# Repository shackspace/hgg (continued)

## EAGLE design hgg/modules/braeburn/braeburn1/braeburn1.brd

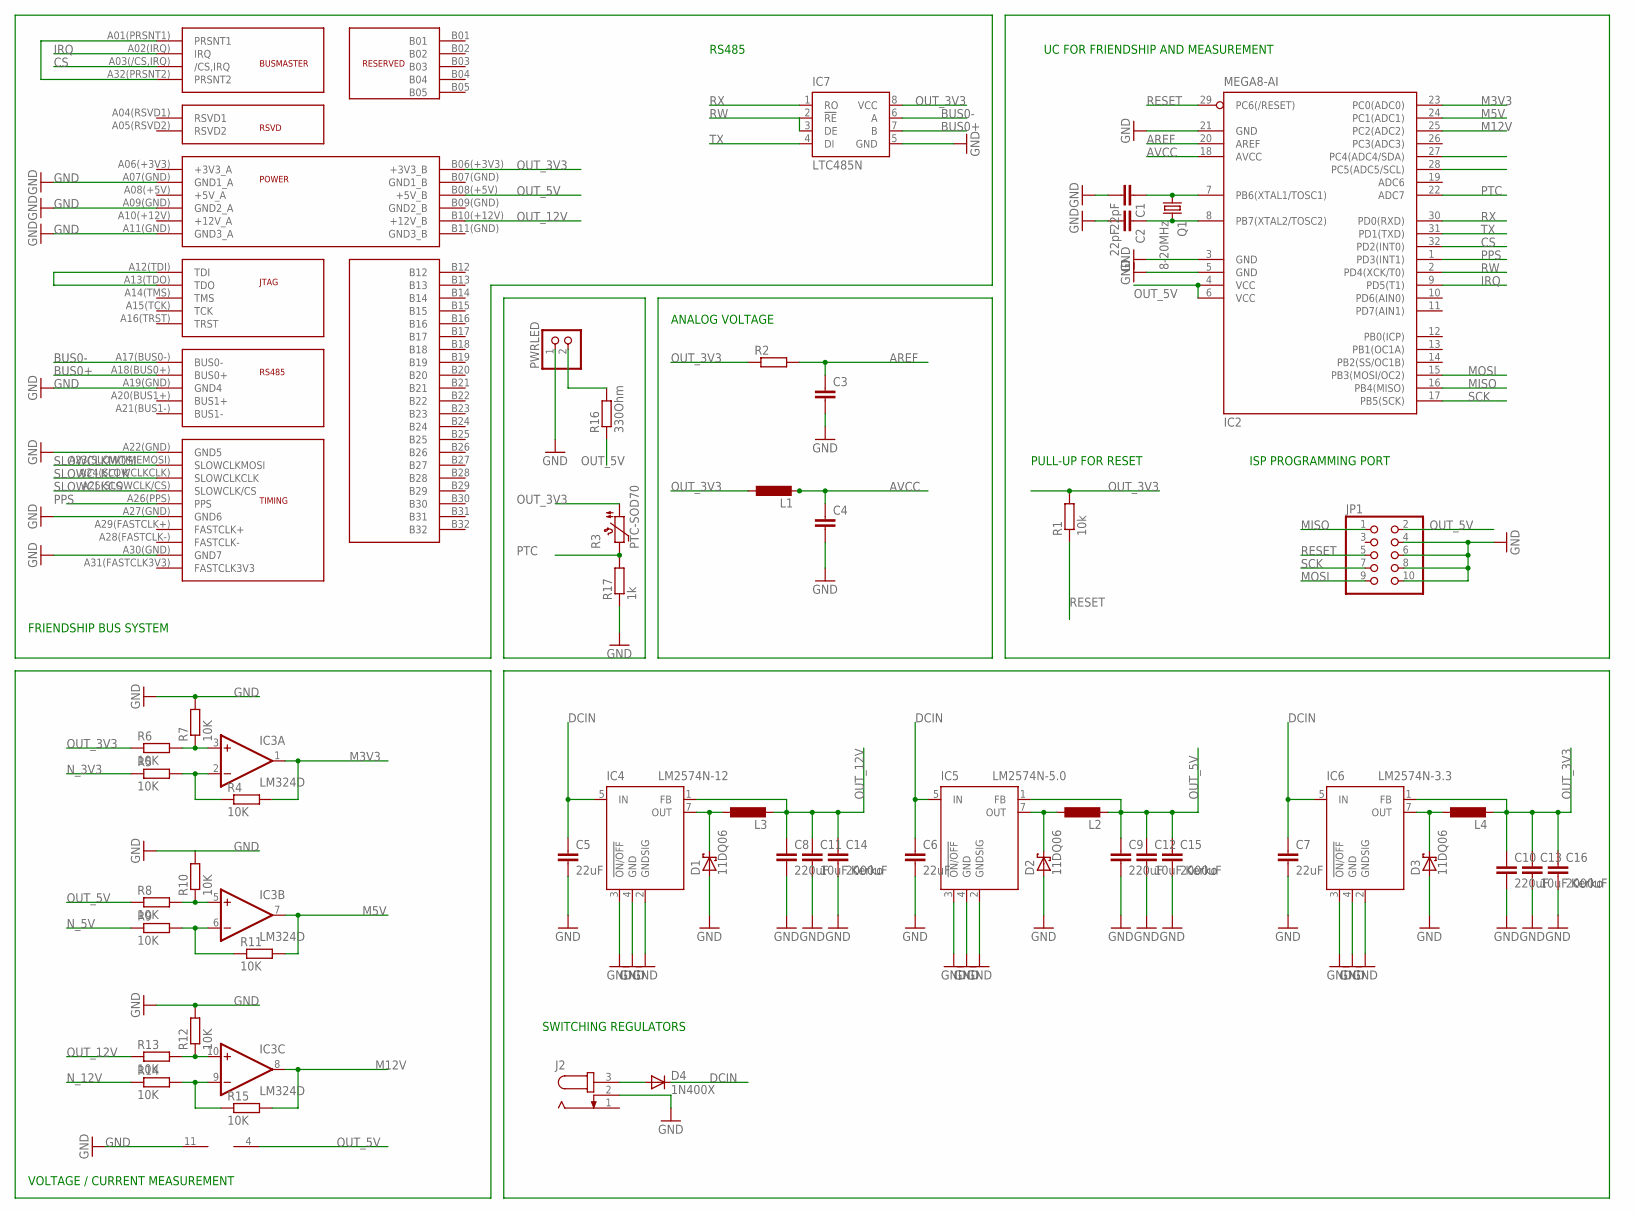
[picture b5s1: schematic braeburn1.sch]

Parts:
C1, C2: 22pF; C0603
C3, C4: C-EUC0603; C0603
C5, C6, C7: 22uF; C025-050X050
C8, C9, C10: 220uF; C025-050X050
C11, C12, C13: 10uF Kerko; C0603
C14, C15, C16: 2000uF; C050-075X075
D1, D2, D3: 11DQ06; DO41-7.6
D4: 1N400X; DO41-10
IC2: MEGA8-AI; TQFP32-08
IC3: LM324D; SO14
IC4: LM2574N-12; DIL08
IC5: LM2574N-5.0; DIL08
IC6: LM2574N-3.3; DIL08
IC7: LTC485N; DIL08
J2: JACK-PLUG0; SPC4077
JP1: PINHD-2X5; 2X05
L1: L-EU0207/5V; 0207/5V
L2, L3, L4: L-EUPIS2816; PIS2816
PWRLED: PINHD-1X2; 1X02
Q1: 8-20MHz; HC49/S
R1: 10k; R0603
R2: R-EU_R0603; R0603
R3: PTC-SOD70; SOD70
R4, R5, R6, R7, R8, R9, R10, R11, R12, R13, R14, R15: 10K; R0603
R16: 330Ohm; R0603
R17: 1k; 0207/12
U$1: FRIENDSHIPCONNECTOR; FRIENDSHIP_EDGE_CONNECTOR

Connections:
AREF: C3.1, IC2.20 (AREF), R2.2
AVCC: C4.1, IC2.18 (AVCC), L1.2
BUS0+: IC7.7 (B), U$1.A18(BUS0+) (BUS0+)
BUS0-: IC7.6 (A), U$1.A17(BUS0-) (BUS0-)
CS: IC2.32 (PD2(INT0)), U$1.A03(/CS,IRQ) (/CS,IRQ)
DCIN: C5.1, C6.1, C7.1, D4.C, IC4.5 (IN), IC5.5 (IN), IC6.5 (IN)
GND: C1.2, C2.2, C3.2, C4.2, C5.2, C6.2, C7.2, C8.2, C9.2, C10.2, C11.2, C12.2, C13.2, C14.2, C15.2, C16.2, D1.A, D2.A, D3.A, IC2.3 (GND), IC2.5 (GND), IC2.21 (GND), IC3.11 (V-), IC4.2 (GNDSIG), IC4.3 (!ON/OFF), IC4.4 (GND), IC5.2 (GNDSIG), IC5.3 (!ON/OFF), IC5.4 (GND), IC6.2 (GNDSIG), IC6.3 (!ON/OFF), IC6.4 (GND), IC7.5 (GND), J2.2, JP1.4, JP1.6, JP1.8, JP1.10, PWRLED.1, R7.2, R10.2, R12.2, R17.1, U$1.A07(GND) (GND1_A), U$1.A09(GND) (GND2_A), U$1.A11(GND) (GND3_A), U$1.A19(GND) (GND4), U$1.A22(GND) (GND5), U$1.A30(GND) (GND7)
IRQ: IC2.9 (PD5(T1)), U$1.A02(IRQ) (IRQ)
M3V3: IC2.23 (PC0(ADC0)), IC3.1 (OUT), R4.2
M5V: IC2.24 (PC1(ADC1)), IC3.7 (OUT), R11.2
M12V: IC2.25 (PC2(ADC2)), IC3.8 (OUT), R15.2
MISO: IC2.16 (PB4(MISO)), JP1.1
MOSI: IC2.15 (PB3(MOSI/OC2)), JP1.9
unnamed: U$1.A01(PRSNT1) (PRSNT1), U$1.A32(PRSNT2) (PRSNT2)
unnamed: U$1.A12(TDI) (TDI), U$1.A13(TDO) (TDO)
unnamed: C1.1, IC2.7 (PB6(XTAL1/TOSC1)), Q1.1
unnamed: C2.1, IC2.8 (PB7(XTAL2/TOSC2)), Q1.2
unnamed: IC3.2 (-IN), R4.1, R5.2
unnamed: IC3.3 (+IN), R6.2, R7.1
unnamed: IC3.6 (-IN), R9.2, R11.1
unnamed: D4.A, J2.3
unnamed: IC3.5 (+IN), R8.2, R10.1
unnamed: PWRLED.2, R16.2
unnamed: IC3.10 (+IN), R12.1, R13.2
unnamed: IC3.9 (-IN), R14.2, R15.1
N_3V3: D3.C, IC6.7 (OUT), L4.1, R5.1
N_5V: D2.C, IC5.7 (OUT), L2.1, R9.1
N_12V: D1.C, IC4.7 (OUT), L3.1, R14.1
OUT_3V3: C10.1, C13.1, C16.1, IC6.1 (FB), IC7.8 (VCC), L1.1, L4.2, R1.2, R2.1, R3.1, R6.1, U$1.B06(+3V3) (+3V3_B)
OUT_5V: C9.1, C12.1, C15.1, IC2.4 (VCC), IC2.6 (VCC), IC3.4 (V+), IC5.1 (FB), JP1.2, L2.2, R8.1, R16.1, U$1.B08(+5V) (+5V_B)
OUT_12V: C8.1, C11.1, C14.1, IC4.1 (FB), L3.2, R13.1, U$1.B10(+12V) (+12V_B)
PPS: IC2.1 (PD3(INT1)), U$1.A26(PPS) (PPS)
PTC: IC2.22 (ADC7), R3.2, R17.2
RESET: IC2.29 (PC6(/RESET)), JP1.5, R1.1
RW: IC2.2 (PD4(XCK/T0)), IC7.2 (!RE), IC7.3 (DE)
RX: IC2.30 (PD0(RXD)), IC7.1 (RO)
SCK: IC2.17 (PB5(SCK)), JP1.7
SLOWCLKCLK: U$1.A24(SLOWCLKCLK) (SLOWCLKCLK)
SLOWCLKCS: U$1.A25(SLOWCLK/CS) (SLOWCLK/CS)
SLOWCLKMOSI: U$1.A23(SLOWTIMEMOSI) (SLOWCLKMOSI)
TX: IC2.31 (PD1(TXD)), IC7.4 (DI)

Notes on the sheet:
FRIENDSHIP BUS SYSTEM
RS485
PULL-UP FOR RESET
ISP PROGRAMMING PORT
UC FOR FRIENDSHIP AND MEASUREMENT
ANALOG VOLTAGE
VOLTAGE / CURRENT MEASUREMENT
SWITCHING REGULATORS

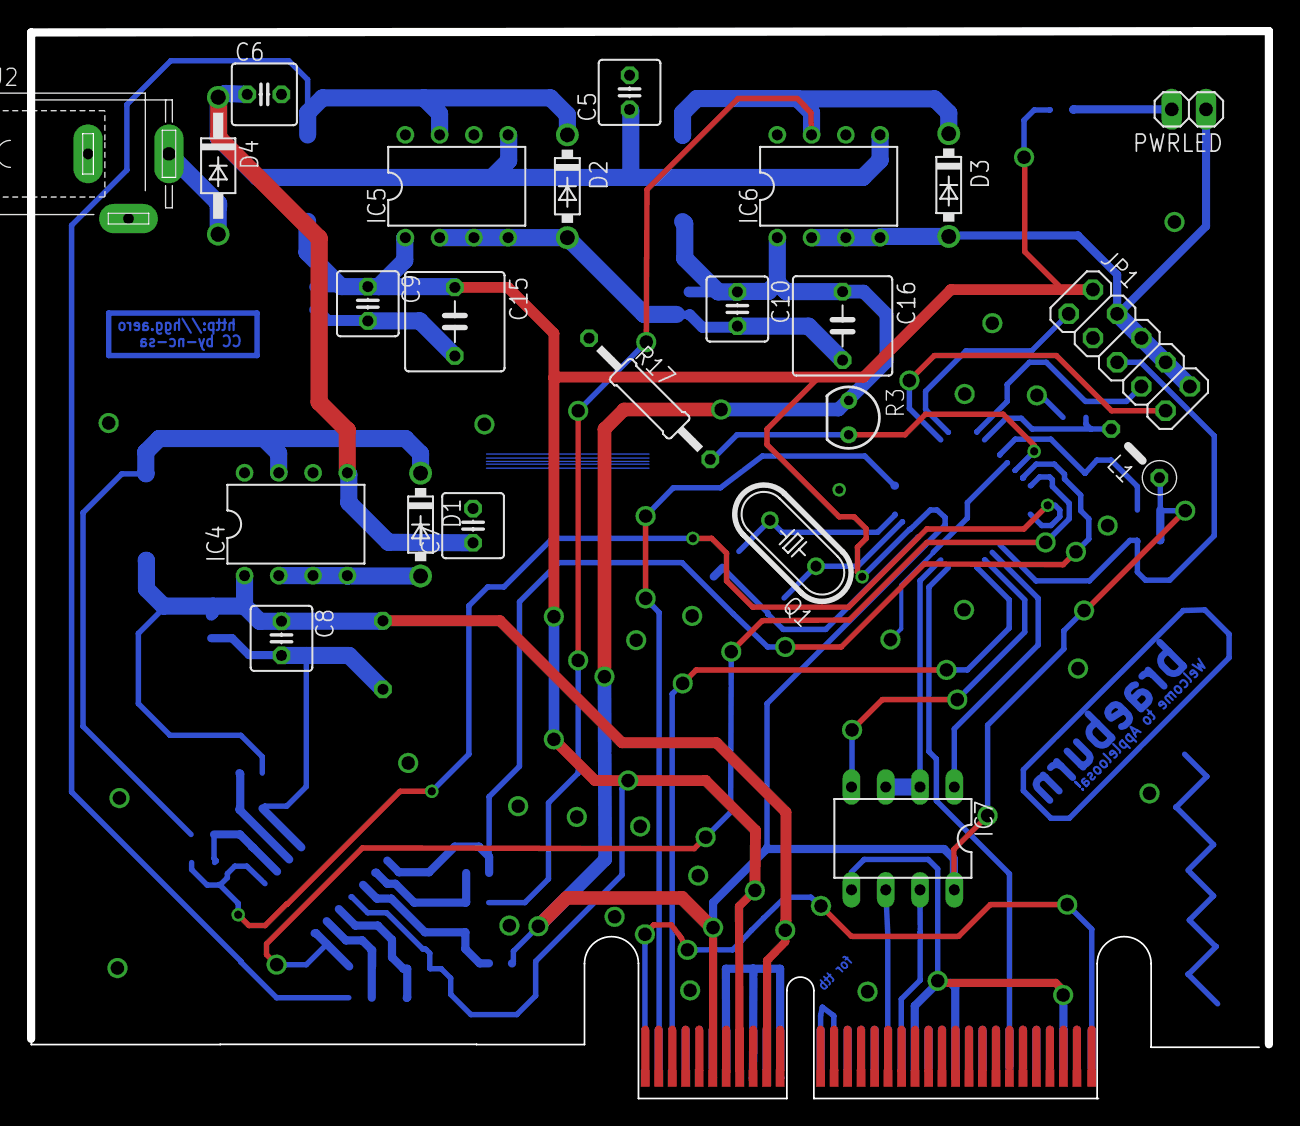
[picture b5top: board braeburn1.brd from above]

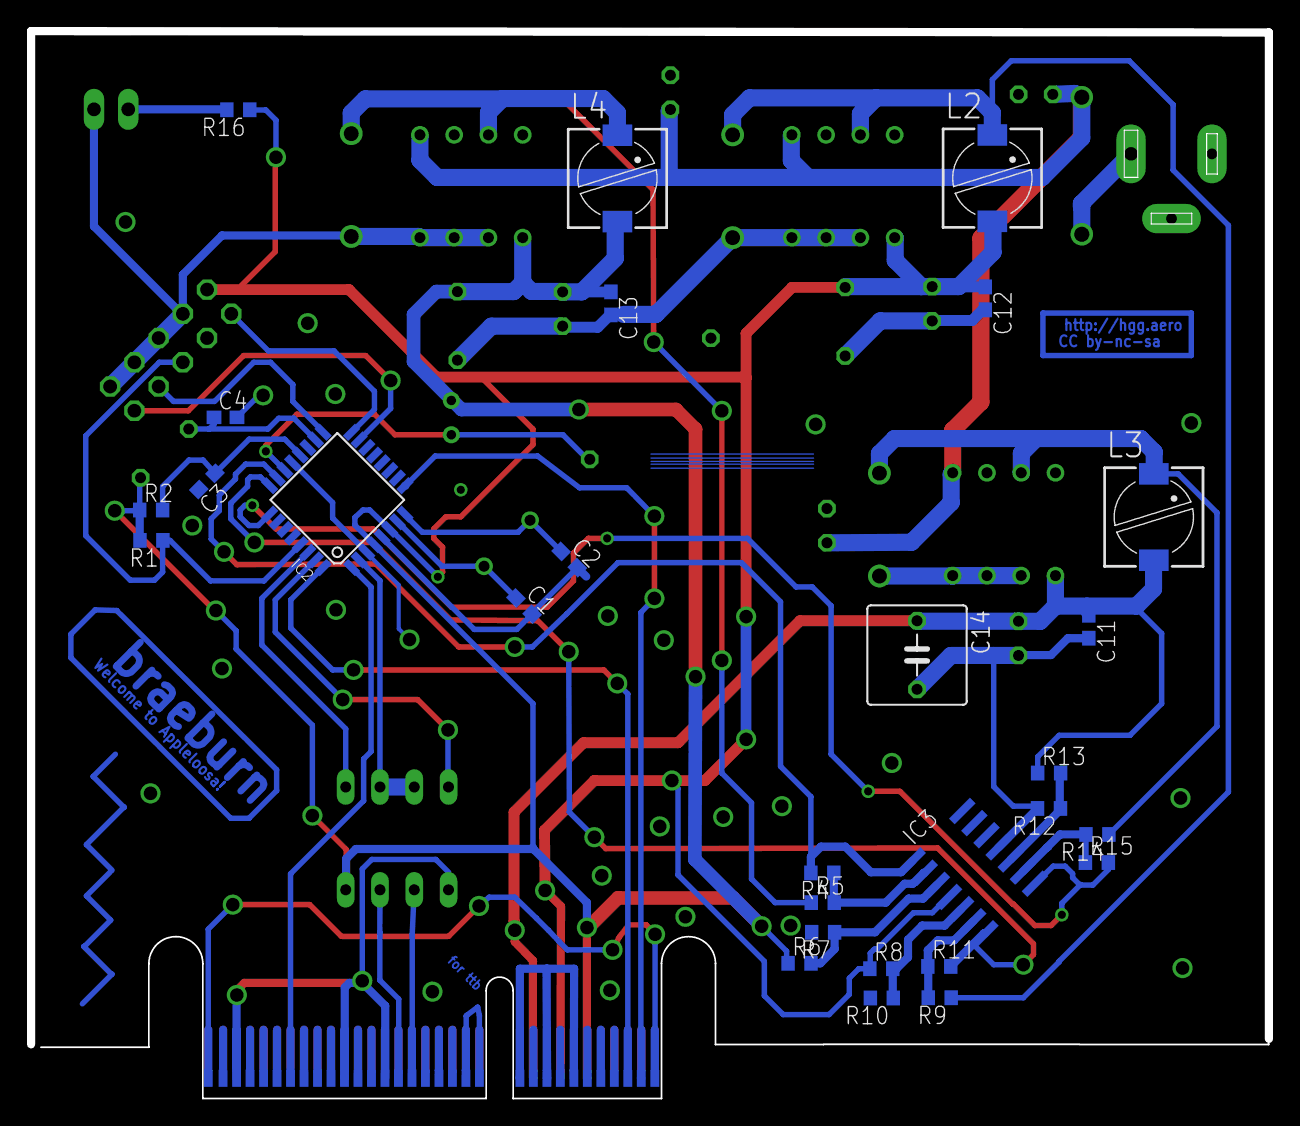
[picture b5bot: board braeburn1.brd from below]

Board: 2 copper layers, 91.8 x 79.1 mm, 52 parts (28 on the bottom side), 38 nets.

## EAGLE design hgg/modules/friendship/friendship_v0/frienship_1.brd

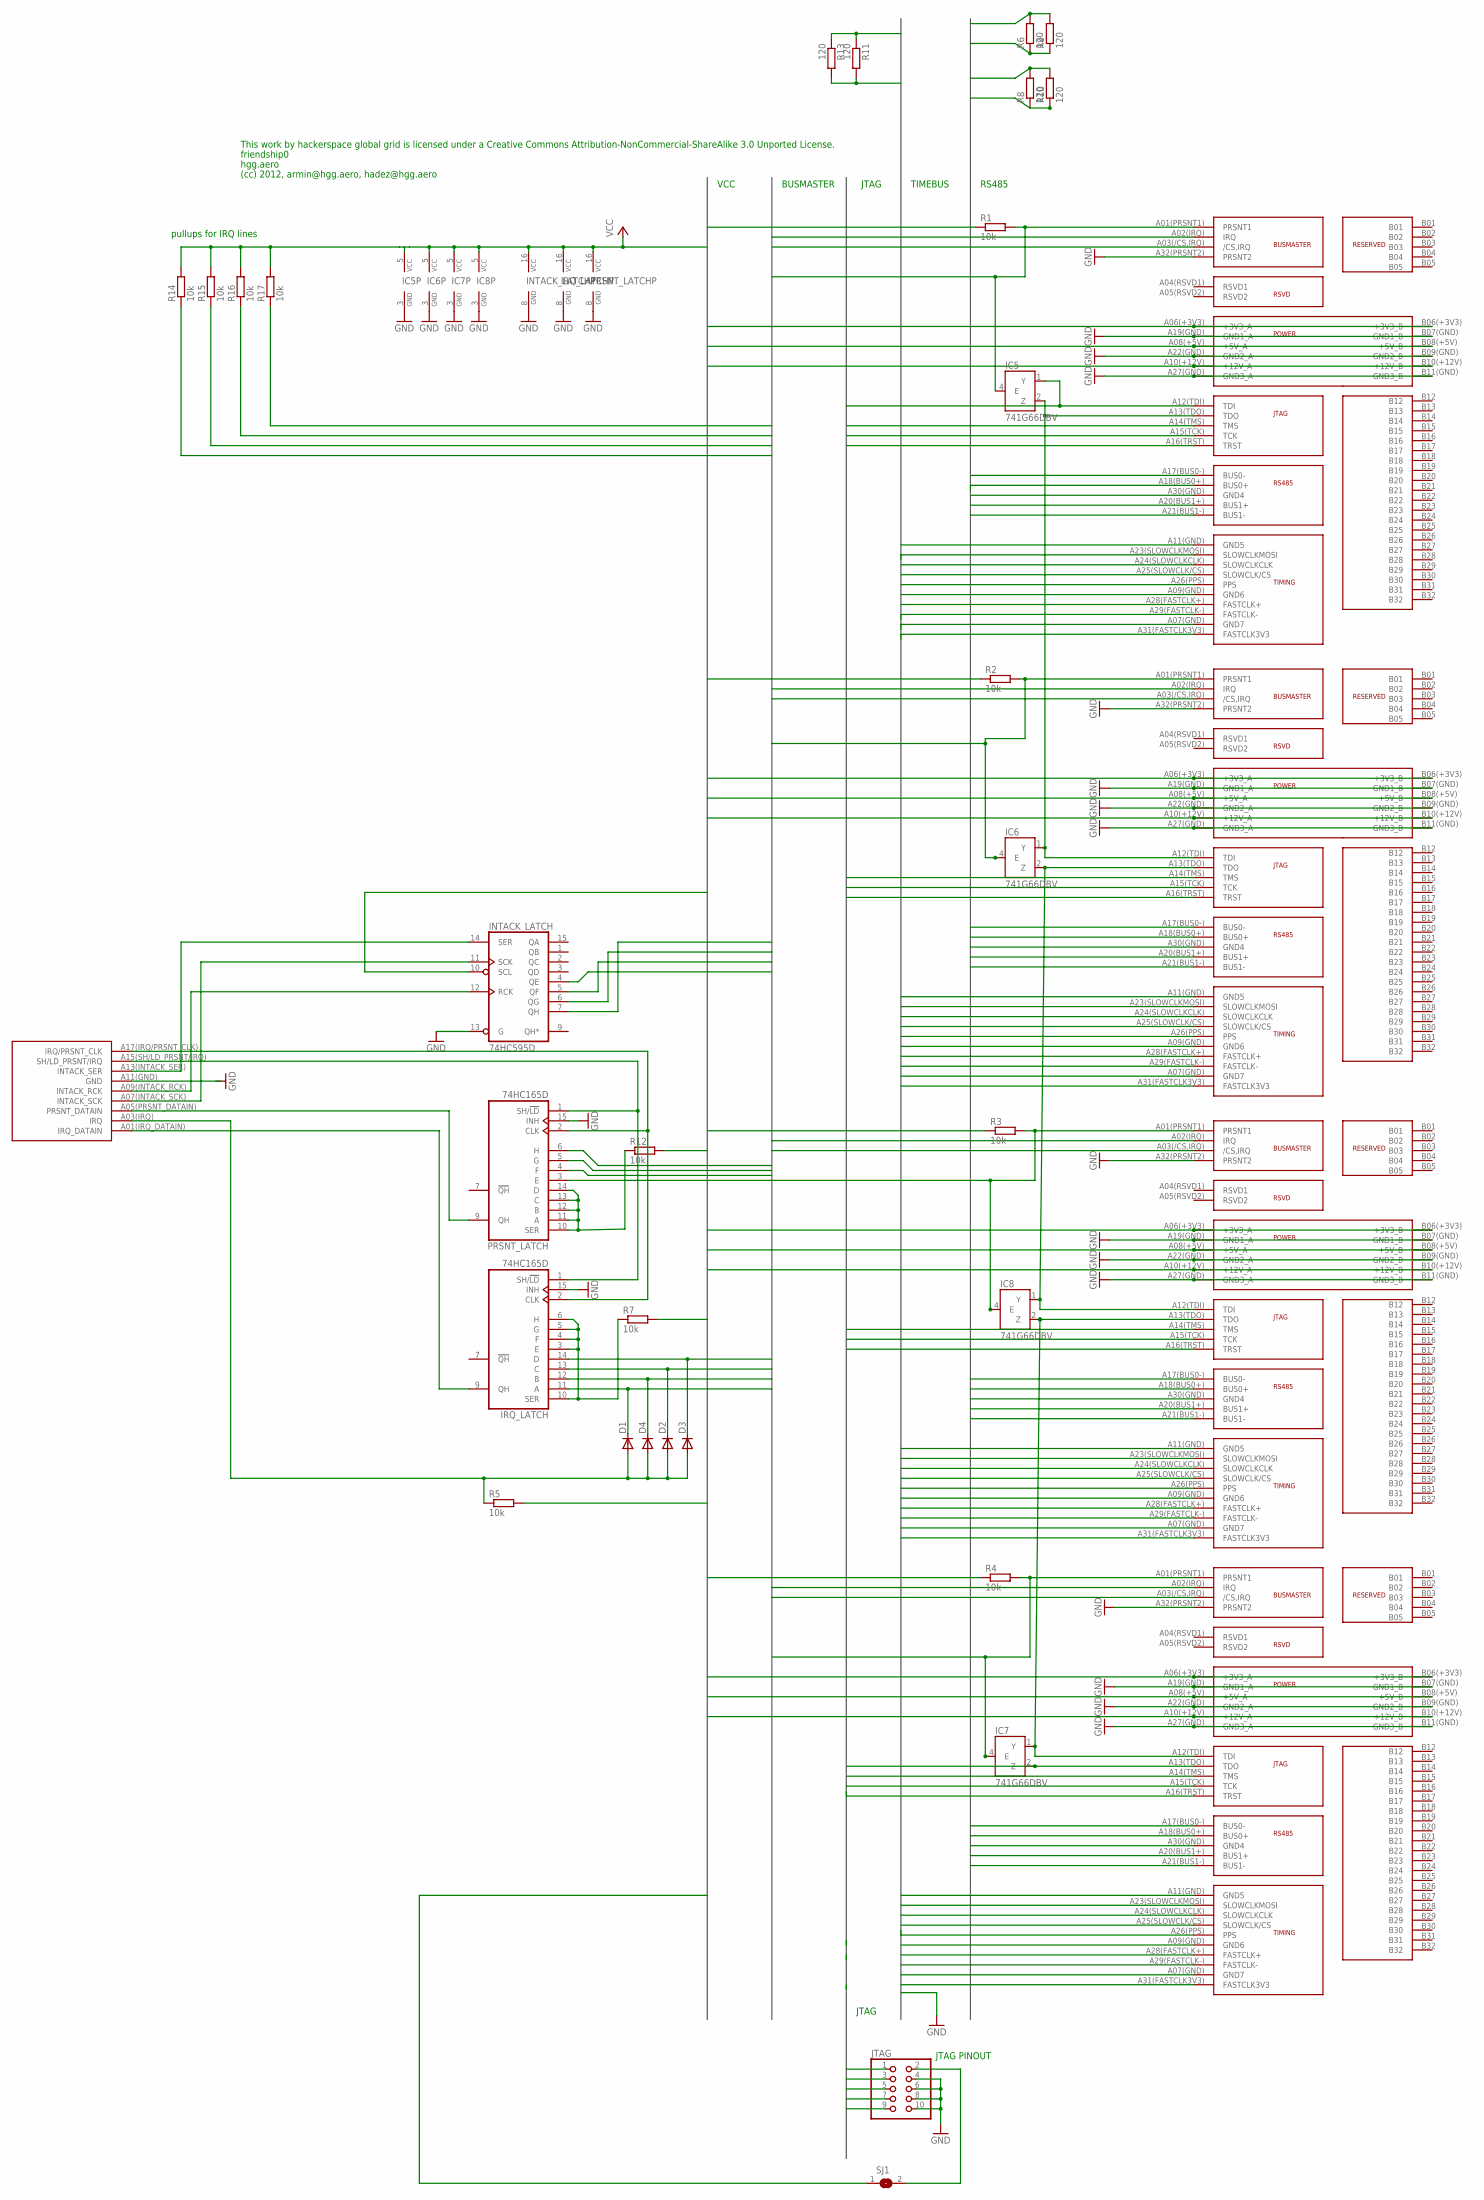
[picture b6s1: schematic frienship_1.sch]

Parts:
D1, D2, D3, D4: DIODE-SOD80C; SOD80C
IC5, IC6, IC7, IC8: 741G66DBV; SOT23-5
INTACK_LATCH: 74HC595D; SO16
IRQ_LATCH: 74HC165D; SO16
JTAG: PINHD-2X5; 2X05
PORT0, PORT1, PORT2, PORT3: FRIENDSHIPSLOT; FRIENDSHIP_SLOT
PRSNT_LATCH: 74HC165D; SO16
R1, R2, R3, R4, R5, R7, R12, R14, R15, R16, R17: 10k; R0603
R6, R8, R9, R10, R11, R13: 120; R0603
SJ1: SJ
U$1: BUSMASTER_PLUG; BUSMASTER_SLOT

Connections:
3V3: IC5.5 (VCC), IC6.5 (VCC), IC7.5 (VCC), IC8.5 (VCC), INTACK_LATCH.10 (SCL), INTACK_LATCH.16 (VCC), IRQ_LATCH.16 (VCC), PORT0.A06(+3V3) (+3V3_A), PORT0.B06(+3V3) (+3V3_B), PORT1.A06(+3V3) (+3V3_A), PORT1.B06(+3V3) (+3V3_B), PORT2.A06(+3V3) (+3V3_A), PORT2.B06(+3V3) (+3V3_B), PORT3.A06(+3V3) (+3V3_A), PORT3.B06(+3V3) (+3V3_B), PRSNT_LATCH.16 (VCC), R1.1, R2.1, R3.1, R4.1, R5.2, R7.2, R12.2, R14.2, R15.2, R16.2, R17.2, SJ1.1
5V: PORT0.A08(+5V) (+5V_A), PORT0.B08(+5V) (+5V_B), PORT1.A08(+5V) (+5V_A), PORT1.B08(+5V) (+5V_B), PORT2.A08(+5V) (+5V_A), PORT2.B08(+5V) (+5V_B), PORT3.A08(+5V) (+5V_A), PORT3.B08(+5V) (+5V_B)
12V: PORT0.A10(+12V) (+12V_A), PORT0.B10(+12V) (+12V_B), PORT1.A10(+12V) (+12V_A), PORT1.B10(+12V) (+12V_B), PORT2.A10(+12V) (+12V_A), PORT2.B10(+12V) (+12V_B), PORT3.A10(+12V) (+12V_A), PORT3.B10(+12V) (+12V_B)
/CS: PORT0.A25(SLOWCLK/CS) (SLOWCLK/CS), PORT1.A25(SLOWCLK/CS) (SLOWCLK/CS), PORT2.A25(SLOWCLK/CS) (SLOWCLK/CS), PORT3.A25(SLOWCLK/CS) (SLOWCLK/CS)
/CS0: INTACK_LATCH.7 (QH), PORT0.A03(/CS,IRQ) (/CS,IRQ)
/CS1: INTACK_LATCH.6 (QG), PORT1.A03(/CS,IRQ) (/CS,IRQ)
/CS2: INTACK_LATCH.5 (QF), PORT2.A03(/CS,IRQ) (/CS,IRQ)
/CS3: INTACK_LATCH.4 (QE), PORT3.A03(/CS,IRQ) (/CS,IRQ)
CLK: PORT0.A24(SLOWCLKCLK) (SLOWCLKCLK), PORT1.A24(SLOWCLKCLK) (SLOWCLKCLK), PORT2.A24(SLOWCLKCLK) (SLOWCLKCLK), PORT3.A24(SLOWCLKCLK) (SLOWCLKCLK)
FASTCLK3V3: PORT0.A31(FASTCLK3V3) (FASTCLK3V3), PORT1.A31(FASTCLK3V3) (FASTCLK3V3), PORT2.A31(FASTCLK3V3) (FASTCLK3V3), PORT3.A31(FASTCLK3V3) (FASTCLK3V3)
FASTCLK+: PORT0.A28(FASTCLK+) (FASTCLK+), PORT1.A28(FASTCLK+) (FASTCLK+), PORT2.A28(FASTCLK+) (FASTCLK+), PORT3.A28(FASTCLK+) (FASTCLK+), R11.1, R13.1
FASTCLK-: PORT0.A29(FASTCLK-) (FASTCLK-), PORT1.A29(FASTCLK-) (FASTCLK-), PORT2.A29(FASTCLK-) (FASTCLK-), PORT3.A29(FASTCLK-) (FASTCLK-), R11.2, R13.2
GND: IC5.3 (GND), IC6.3 (GND), IC7.3 (GND), IC8.3 (GND), INTACK_LATCH.8 (GND), INTACK_LATCH.13 (G), IRQ_LATCH.8 (GND), IRQ_LATCH.15 (INH), JTAG.4, JTAG.6, JTAG.8, JTAG.10, PORT0.A07(GND) (GND7), PORT0.A09(GND) (GND6), PORT0.A11(GND) (GND5), PORT0.A19(GND) (GND1_A), PORT0.A22(GND) (GND2_A), PORT0.A27(GND) (GND3_A), PORT0.A30(GND) (GND4), PORT0.A32(PRSNT2) (PRSNT2), PORT0.B07(GND) (GND1_B), PORT0.B09(GND) (GND2_B), PORT0.B11(GND) (GND3_B), PORT1.A07(GND) (GND7), PORT1.A09(GND) (GND6), PORT1.A11(GND) (GND5), PORT1.A19(GND) (GND1_A), PORT1.A22(GND) (GND2_A), PORT1.A27(GND) (GND3_A), PORT1.A30(GND) (GND4), PORT1.A32(PRSNT2) (PRSNT2), PORT1.B07(GND) (GND1_B), PORT1.B09(GND) (GND2_B), PORT1.B11(GND) (GND3_B), PORT2.A07(GND) (GND7), PORT2.A09(GND) (GND6), PORT2.A11(GND) (GND5), PORT2.A19(GND) (GND1_A), PORT2.A22(GND) (GND2_A), PORT2.A27(GND) (GND3_A), PORT2.A30(GND) (GND4), PORT2.A32(PRSNT2) (PRSNT2), PORT2.B07(GND) (GND1_B), PORT2.B09(GND) (GND2_B), PORT2.B11(GND) (GND3_B), PORT3.A07(GND) (GND7), PORT3.A09(GND) (GND6), PORT3.A11(GND) (GND5), PORT3.A19(GND) (GND1_A), PORT3.A22(GND) (GND2_A), PORT3.A27(GND) (GND3_A), PORT3.A30(GND) (GND4), PORT3.A32(PRSNT2) (PRSNT2), PORT3.B07(GND) (GND1_B), PORT3.B09(GND) (GND2_B), PORT3.B11(GND) (GND3_B), PRSNT_LATCH.8 (GND), PRSNT_LATCH.15 (INH)
IRQ0: D3.C, IRQ_LATCH.14 (D), PORT0.A02(IRQ) (IRQ), R17.1
IRQ1: D2.C, IRQ_LATCH.13 (C), PORT1.A02(IRQ) (IRQ), R16.1
IRQ2: D4.C, IRQ_LATCH.12 (B), PORT2.A02(IRQ) (IRQ), R15.1
IRQ3: D1.C, IRQ_LATCH.11 (A), PORT3.A02(IRQ) (IRQ), R14.1
MOSI: PORT0.A23(SLOWCLKMOSI) (SLOWCLKMOSI), PORT1.A23(SLOWCLKMOSI) (SLOWCLKMOSI), PORT2.A23(SLOWCLKMOSI) (SLOWCLKMOSI), PORT3.A23(SLOWCLKMOSI) (SLOWCLKMOSI)
unnamed: INTACK_LATCH.14 (SER), U$1.A13(INTACK_SER) (INTACK_SER)
unnamed: IC5.2 (Z), IC6.1 (Y), PORT0.A13(TDO) (TDO), PORT1.A12(TDI) (TDI)
unnamed: IRQ_LATCH.1 (SH/!LD), PRSNT_LATCH.1 (SH/!LD), U$1.A15(SH/LD_PRSNT/IRQ) (SH/LD_PRSNT/IRQ)
unnamed: INTACK_LATCH.11 (SCK), U$1.A07(INTACK_SCK) (INTACK_SCK)
unnamed: JTAG.2, SJ1.2
unnamed: IC6.2 (Z), IC8.1 (Y), PORT1.A13(TDO) (TDO), PORT2.A12(TDI) (TDI)
unnamed: IC7.1 (Y), IC8.2 (Z), PORT2.A13(TDO) (TDO), PORT3.A12(TDI) (TDI)
unnamed: IRQ_LATCH.3 (E), IRQ_LATCH.4 (F), IRQ_LATCH.5 (G), IRQ_LATCH.6 (H), IRQ_LATCH.10 (SER), R7.1
unnamed: INTACK_LATCH.12 (RCK), U$1.A09(INTACK_RCK) (INTACK_RCK)
unnamed: PRSNT_LATCH.10 (SER), PRSNT_LATCH.11 (A), PRSNT_LATCH.12 (B), PRSNT_LATCH.13 (C), PRSNT_LATCH.14 (D), R12.1
unnamed: D1.A, D2.A, D3.A, D4.A, R5.1, U$1.A03(IRQ) (IRQ)
unnamed: PRSNT_LATCH.9 (QH), U$1.A05(PRSNT_DATAIN) (PRSNT_DATAIN)
unnamed: IRQ_LATCH.9 (QH), U$1.A01(IRQ_DATAIN) (IRQ_DATAIN)
PPS: PORT0.A26(PPS) (PPS), PORT1.A26(PPS) (PPS), PORT2.A26(PPS) (PPS), PORT3.A26(PPS) (PPS)
PRSNT0: IC5.4 (E), PORT0.A01(PRSNT1) (PRSNT1), PRSNT_LATCH.6 (H), R1.2
PRSNT1: IC6.4 (E), PORT1.A01(PRSNT1) (PRSNT1), PRSNT_LATCH.5 (G), R2.2
PRSNT2: IC8.4 (E), PORT2.A01(PRSNT1) (PRSNT1), PRSNT_LATCH.4 (F), R3.2
PRSNT3: IC7.4 (E), PORT3.A01(PRSNT1) (PRSNT1), PRSNT_LATCH.3 (E), R4.2
RX+: PORT0.A20(BUS1+) (BUS1+), PORT1.A20(BUS1+) (BUS1+), PORT2.A20(BUS1+) (BUS1+), PORT3.A20(BUS1+) (BUS1+), R8.2, R10.2
RX-: PORT0.A21(BUS1-) (BUS1-), PORT1.A21(BUS1-) (BUS1-), PORT2.A21(BUS1-) (BUS1-), PORT3.A21(BUS1-) (BUS1-), R8.1, R10.1
SHIFT: IRQ_LATCH.2 (CLK), PRSNT_LATCH.2 (CLK), U$1.A17(IRQ/PRSNT_CLK) (IRQ/PRSNT_CLK)
TCK: JTAG.7, PORT0.A15(TCK) (TCK), PORT1.A15(TCK) (TCK), PORT2.A15(TCK) (TCK), PORT3.A15(TCK) (TCK)
TDI: IC5.1 (Y), JTAG.1, PORT0.A12(TDI) (TDI)
TDO: IC7.2 (Z), JTAG.3, PORT3.A13(TDO) (TDO)
TMS: JTAG.5, PORT0.A14(TMS) (TMS), PORT1.A14(TMS) (TMS), PORT2.A14(TMS) (TMS), PORT3.A14(TMS) (TMS)
TRST: JTAG.9, PORT0.A16(TRST) (TRST), PORT1.A16(TRST) (TRST), PORT2.A16(TRST) (TRST), PORT3.A16(TRST) (TRST)
TX+: PORT0.A18(BUS0+) (BUS0+), PORT1.A18(BUS0+) (BUS0+), PORT2.A18(BUS0+) (BUS0+), PORT3.A18(BUS0+) (BUS0+), R6.2, R9.2
TX-: PORT0.A17(BUS0-) (BUS0-), PORT1.A17(BUS0-) (BUS0-), PORT2.A17(BUS0-) (BUS0-), PORT3.A17(BUS0-) (BUS0-), R6.1, R9.1

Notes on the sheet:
RS485
TIMEBUS
JTAG
BUSMASTER
VCC
JTAG PINOUT
friendship0
hgg.aero
This work by hackerspace global grid is licensed under a Creative Commons Attribution-NonCommercial-ShareAlike 3.0 Unported License.
(cc) 2012, armin@hgg.aero, hadez@hgg.aero
pullups for IRQ lines

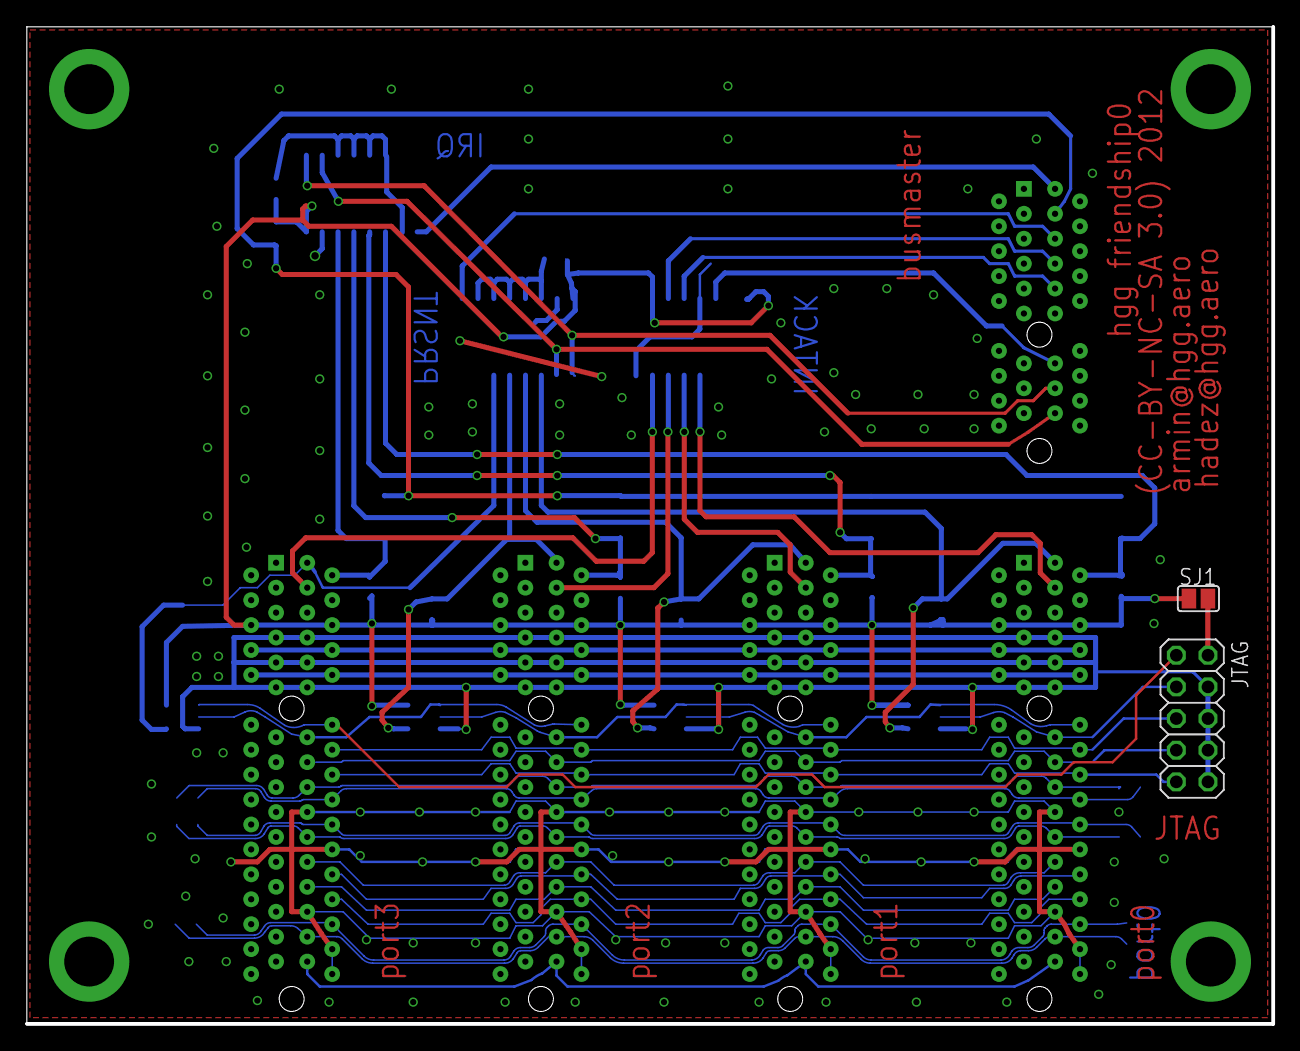
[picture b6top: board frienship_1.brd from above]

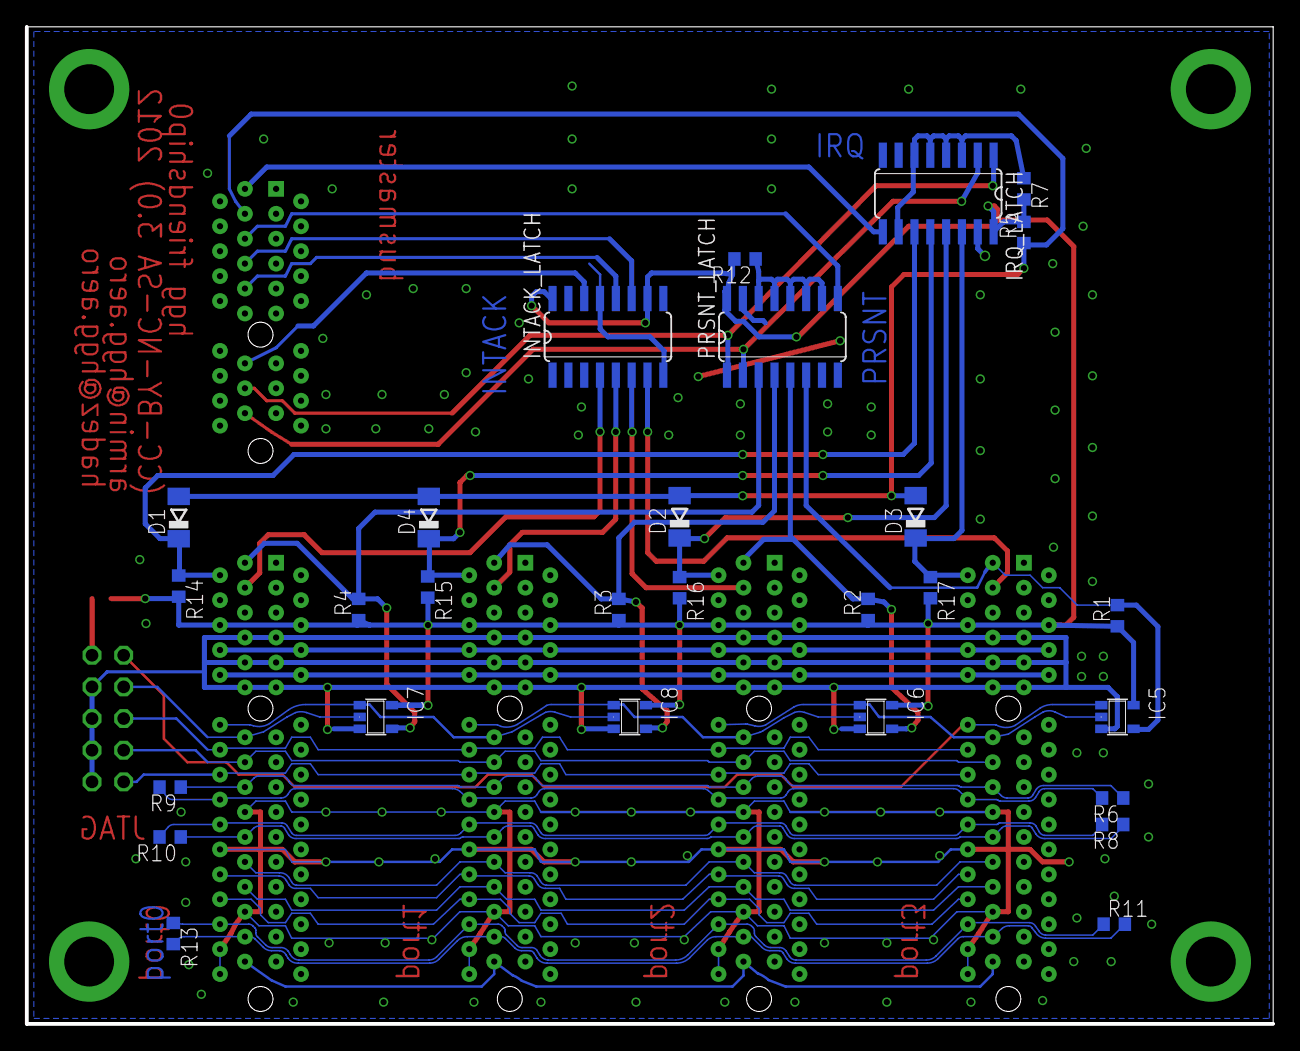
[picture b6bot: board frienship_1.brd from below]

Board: 2 copper layers, 100.0 x 80.0 mm, 35 parts (28 on the bottom side), 46 nets.

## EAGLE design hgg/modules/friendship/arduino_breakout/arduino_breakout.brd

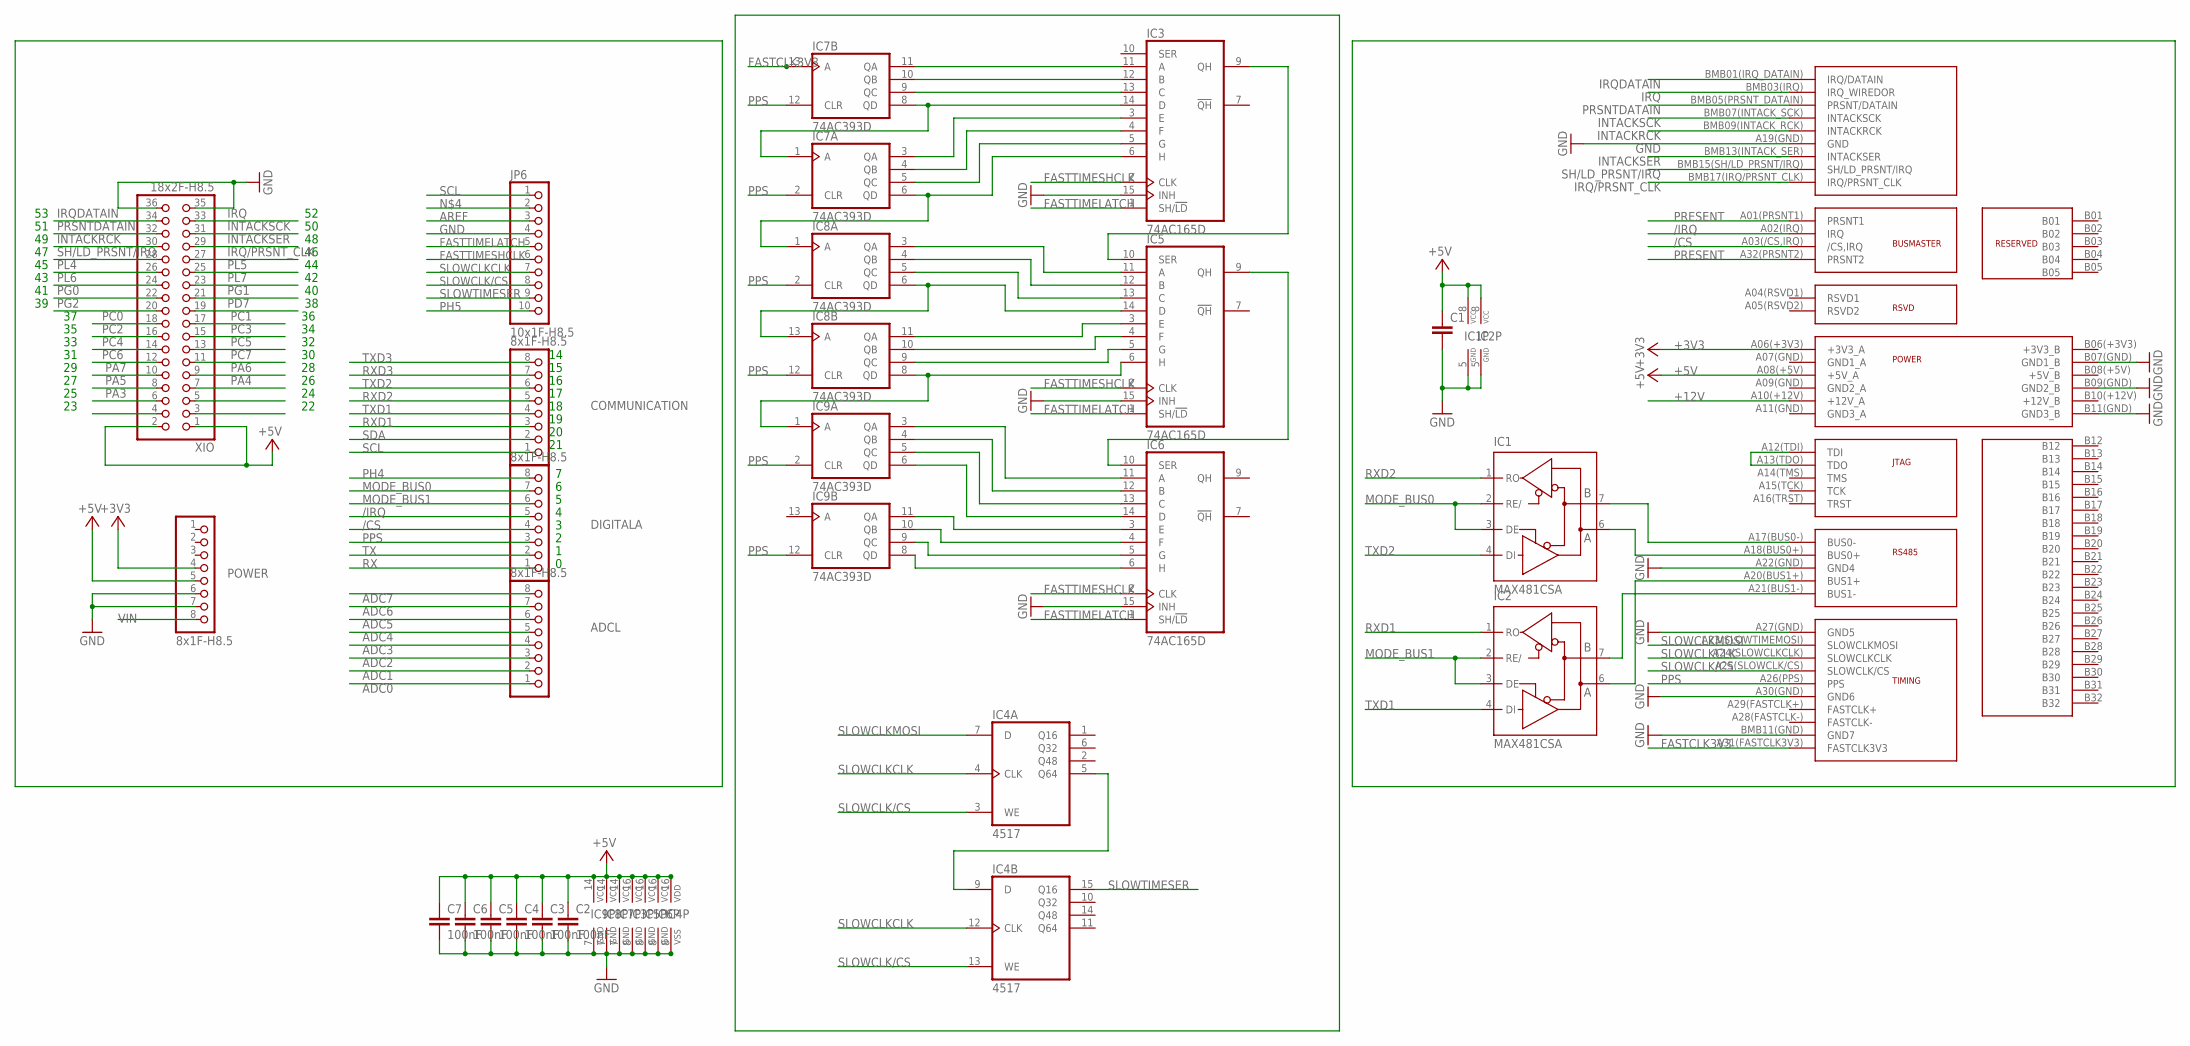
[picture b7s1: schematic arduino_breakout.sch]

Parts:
ADCL: 8x1F-H8.5; 1X08
C1: C-EUC0603; C0603
C2, C3, C4, C5, C6, C7: 100nF; C0603
COMMUNICATION: 8x1F-H8.5; 1X08
DIGITALA: 8x1F-H8.5; 1X08
IC1, IC2: MAX481CSA; SO08
IC3, IC5, IC6: 74AC165D; SO16
IC4: 4517; SO16
IC7, IC8, IC9: 74AC393D; SO14
JP6: 10x1F-H8.5; 1X10
POWER: 8x1F-H8.5; 1X08
U$1: BUSMASTER; BUSMASTER_EDGE_CONNECTOR
XIO: 18x2F-H8.5; 2X18

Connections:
+3V3: POWER.4, U$1.A06(+3V3) (+3V3_A)
+5V: C1.1, C2.1, C3.1, C4.1, C5.1, C6.1, C7.1, IC1.8 (VCC), IC2.8 (VCC), IC3.16 (VCC), IC4.16 (VDD), IC5.16 (VCC), IC6.16 (VCC), IC7.14 (VCC), IC8.14 (VCC), IC9.14 (VCC), POWER.5, U$1.A08(+5V) (+5V_A), XIO.1, XIO.2
+12V: U$1.A10(+12V) (+12V_A)
/CS: DIGITALA.4, U$1.A03(/CS,IRQ) (/CS,IRQ)
/IRQ: DIGITALA.5, U$1.A02(IRQ) (IRQ)
ADC0: ADCL.1
ADC1: ADCL.2
ADC2: ADCL.3
ADC3: ADCL.4
ADC4: ADCL.5
ADC5: ADCL.6
ADC6: ADCL.7
ADC7: ADCL.8
AREF: JP6.3
FASTCLK3V3: IC7.13 (A), U$1.A31(FASTCLK3V3) (FASTCLK3V3)
FASTTIMELATCH: IC3.1 (SH/!LD), IC5.1 (SH/!LD), IC6.1 (SH/!LD), JP6.5
FASTTIMESHCLK: IC3.2 (CLK), IC5.2 (CLK), IC6.2 (CLK), JP6.6
GND: C1.2, C2.2, C3.2, C4.2, C5.2, C6.2, C7.2, IC1.5 (GND), IC2.5 (GND), IC3.8 (GND), IC3.15 (INH), IC4.8 (VSS), IC5.8 (GND), IC5.15 (INH), IC6.8 (GND), IC6.15 (INH), IC7.7 (GND), IC8.7 (GND), IC9.7 (GND), JP6.4, POWER.6, POWER.7, U$1.A19(GND) (GND), U$1.A22(GND) (GND4), U$1.A27(GND) (GND5), U$1.A30(GND) (GND6), U$1.B07(GND) (GND1_B), U$1.B09(GND) (GND2_B), U$1.B11(GND) (GND3_B), U$1.BMB11(GND) (GND7), XIO.35, XIO.36
INTACKRCK: U$1.BMB09(INTACK_RCK) (INTACKRCK), XIO.30
INTACKSCK: U$1.BMB07(INTACK_SCK) (INTACKSCK), XIO.31
INTACKSER: U$1.BMB13(INTACK_SER) (INTACKSER), XIO.29
IRQ: U$1.BMB03(IRQ) (IRQ_WIREDOR), XIO.33
IRQ/PRSNT_CLK: U$1.BMB17(IRQ/PRSNT_CLK) (IRQ/PRSNT_CLK), XIO.27
IRQDATAIN: U$1.BMB01(IRQ_DATAIN) (IRQ/DATAIN), XIO.34
MODE_BUS0: DIGITALA.7, IC1.2 (RE/), IC1.3 (DE)
MODE_BUS1: DIGITALA.6, IC2.2 (RE/), IC2.3 (DE)
unnamed: U$1.A12(TDI) (TDI), U$1.A13(TDO) (TDO)
unnamed: IC1.7 (B), U$1.A17(BUS0-) (BUS0-)
unnamed: IC1.6 (A), U$1.A18(BUS0+) (BUS0+)
unnamed: IC2.7 (B), U$1.A21(BUS1-) (BUS1-)
unnamed: IC2.6 (A), U$1.A20(BUS1+) (BUS1+)
unnamed: IC7.1 (A), IC7.8 (QD)
unnamed: IC3.13 (C), IC7.9 (QC)
unnamed: IC3.12 (B), IC7.10 (QB)
unnamed: IC3.11 (A), IC7.11 (QA)
unnamed: IC3.3 (E), IC7.3 (QA)
unnamed: IC3.4 (F), IC7.4 (QB)
unnamed: IC3.5 (G), IC7.5 (QC)
unnamed: IC3.6 (H), IC7.6 (QD), IC8.1 (A)
unnamed: IC6.6 (H), IC9.8 (QD)
unnamed: IC6.5 (G), IC9.9 (QC)
unnamed: IC6.4 (F), IC9.10 (QB)
unnamed: IC6.3 (E), IC9.11 (QA)
unnamed: IC6.14 (D), IC9.6 (QD)
unnamed: IC6.13 (C), IC9.5 (QC)
unnamed: IC6.12 (B), IC9.4 (QB)
unnamed: IC6.11 (A), IC9.3 (QA)
unnamed: IC5.6 (H), IC8.8 (QD), IC9.1 (A)
unnamed: IC5.5 (G), IC8.9 (QC)
unnamed: IC5.4 (F), IC8.10 (QB)
unnamed: IC5.3 (E), IC8.11 (QA)
unnamed: IC5.14 (D), IC8.6 (QD), IC8.13 (A)
unnamed: IC5.13 (C), IC8.5 (QC)
unnamed: IC4.5 (Q64), IC4.9 (D)
unnamed: IC3.9 (QH), IC5.10 (SER)
unnamed: IC5.12 (B), IC8.4 (QB)
unnamed: IC5.9 (QH), IC6.10 (SER)
unnamed: IC5.11 (A), IC8.3 (QA)
PA3: XIO.6
PA4: XIO.7
PA5: XIO.8
PA6: XIO.9
PA7: XIO.10
PC0: XIO.18
PC1: XIO.17
PC2: XIO.16
PC3: XIO.15
PC4: XIO.14
PC5: XIO.13
PC6: XIO.12
PC7: XIO.11
PD7: XIO.19
PG0: XIO.22
PG1: XIO.21
PG2: XIO.20
PH4: DIGITALA.8
PH5: JP6.10
PL4: XIO.26
PL5: XIO.25
PL6: XIO.24
PL7: XIO.23
PPS: DIGITALA.3, IC7.2 (CLR), IC7.12 (CLR), IC8.2 (CLR), IC8.12 (CLR), IC9.2 (CLR), IC9.12 (CLR), U$1.A26(PPS) (PPS)
PRESENT: U$1.A01(PRSNT1) (PRSNT1), U$1.A32(PRSNT2) (PRSNT2)
PRSNTDATAIN: U$1.BMB05(PRSNT_DATAIN) (PRSNT/DATAIN), XIO.32
RX: DIGITALA.1
RXD1: COMMUNICATION.3, IC2.1 (RO)
RXD2: COMMUNICATION.5, IC1.1 (RO)
RXD3: COMMUNICATION.7
SCL: COMMUNICATION.1, JP6.1
SDA: COMMUNICATION.2
SH/LD_PRSNT/IRQ: U$1.BMB15(SH/LD_PRSNT/I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 (SH/LD_PRSNT/IRQ), XIO.28
SLOWCLK/CS: IC4.3 (WE), IC4.13 (WE), JP6.8, U$1.A25(SLOWCLK/CS) (SLOWCLK/CS)
SLOWCLKCLK: IC4.4 (CLK), IC4.12 (CLK), JP6.7, U$1.A24(SLOWCLKCLK) (SLOWCLKCLK)
SLOWCLKMOSI: IC4.7 (D), U$1.A23(SLOWTIMEMOSI) (SLOWCLKMOSI)
SLOWTIMESER: IC4.15 (Q16), JP6.9
TX: DIGITALA.2
TXD1: COMMUNICATION.4, IC2.4 (DI)
TXD2: COMMUNICATION.6, IC1.4 (DI)
TXD3: COMMUNICATION.8
VIN: POWER.8
